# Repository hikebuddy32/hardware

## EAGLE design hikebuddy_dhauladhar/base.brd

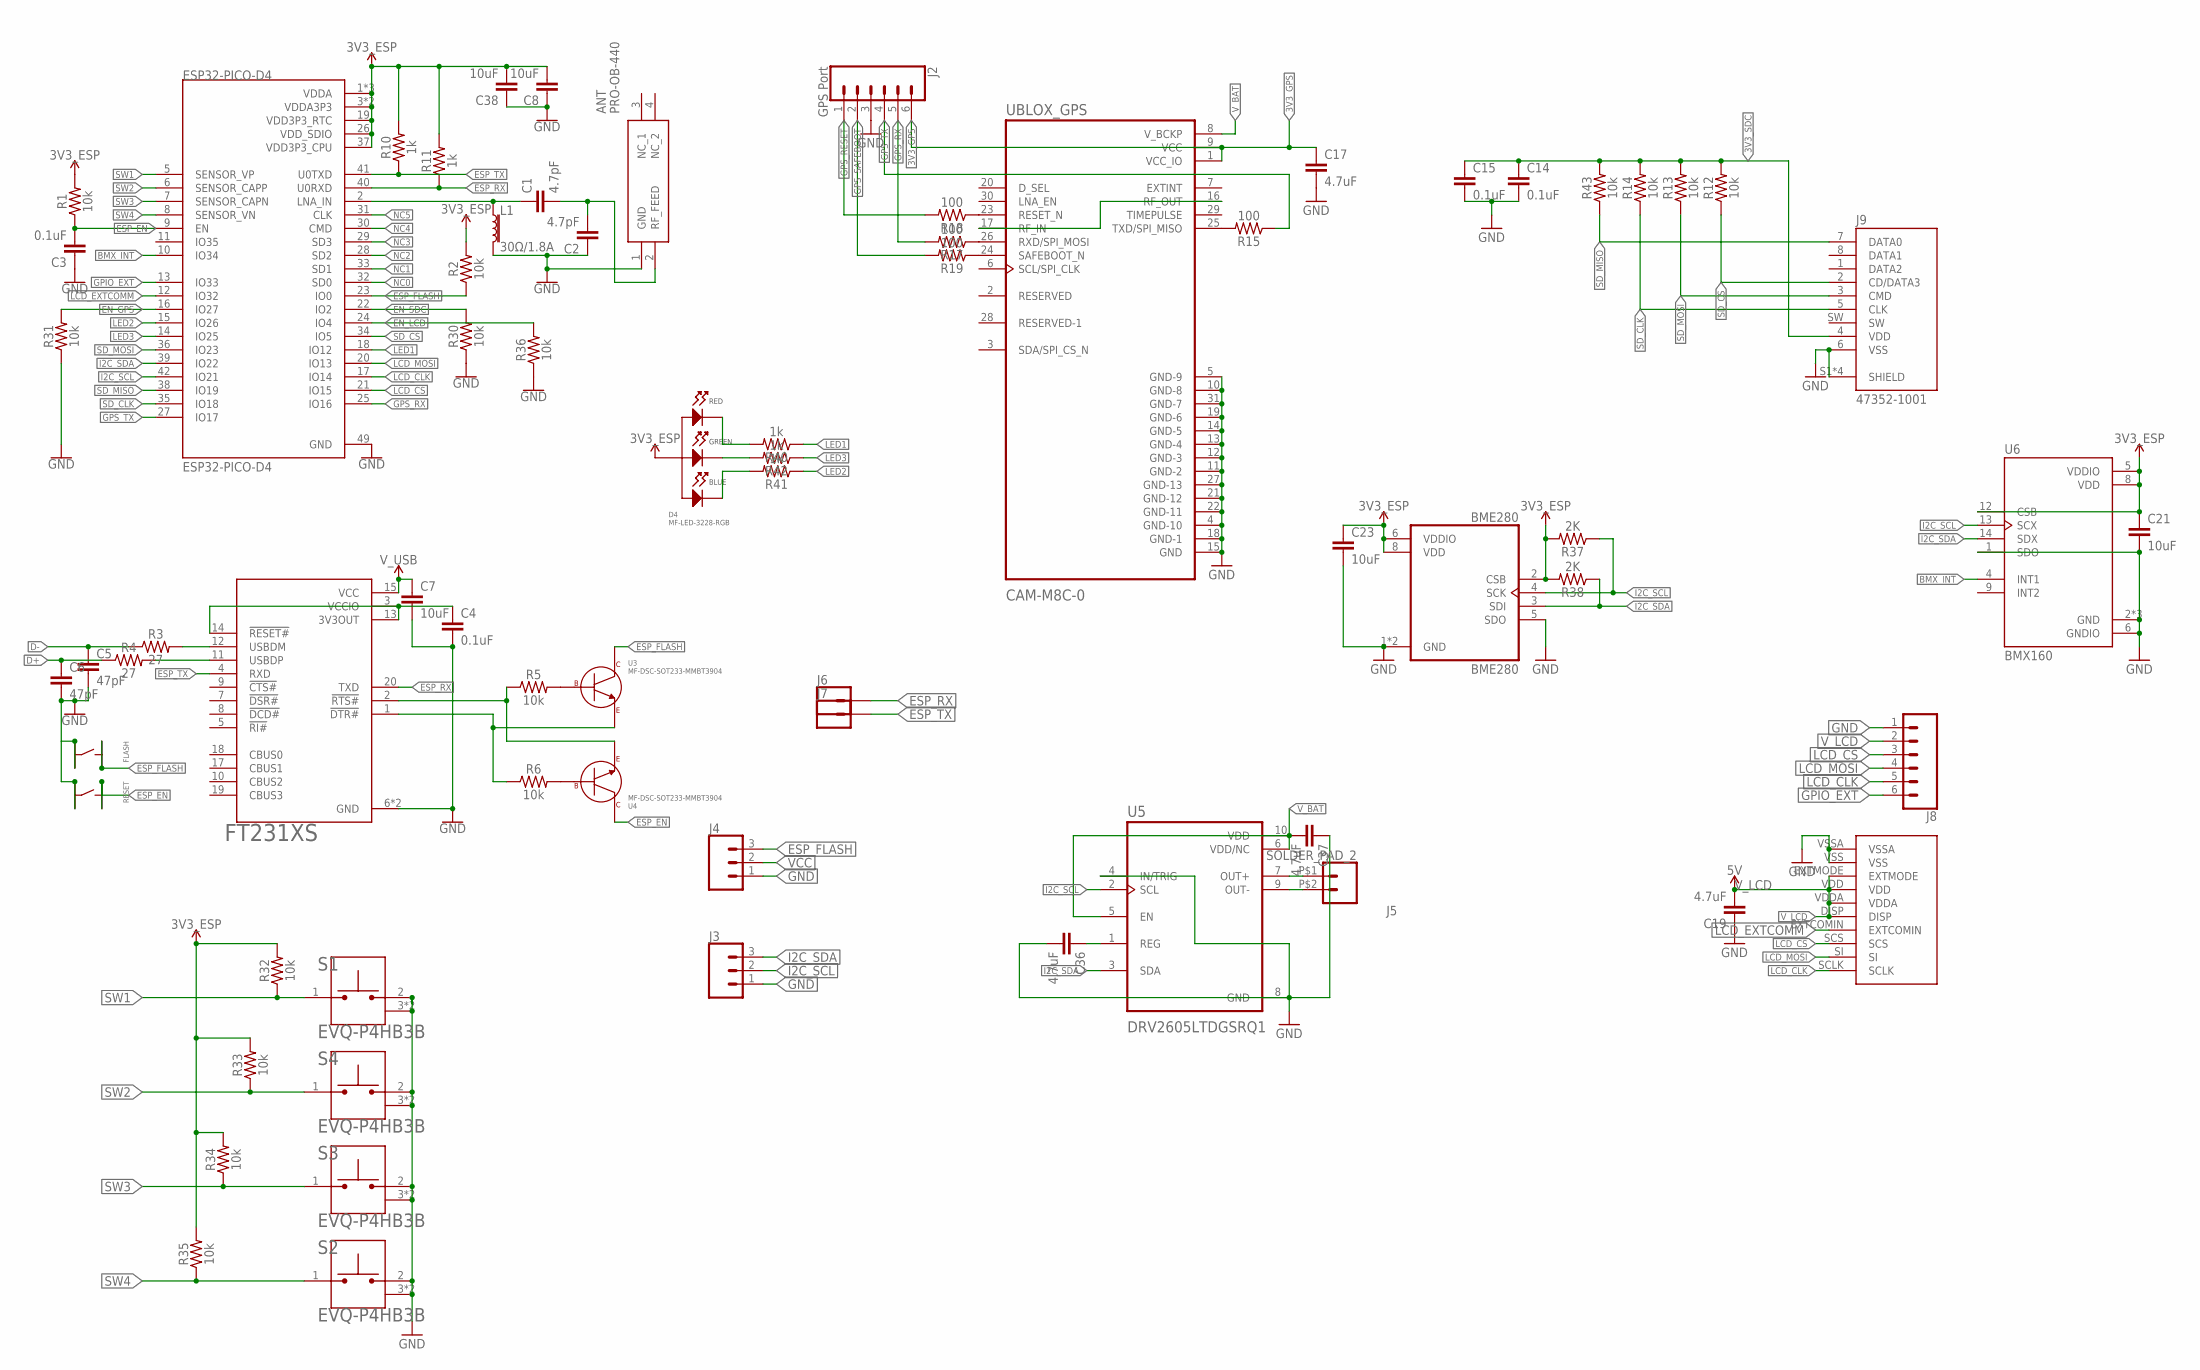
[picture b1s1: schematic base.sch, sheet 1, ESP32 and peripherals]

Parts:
ANT: PRO-OB-440; PRO-OB-440_1
BME280: BME280; PSON65P250X250X100-8N
C1, C2: 4.7pF; C0603
C3, C4, C14, C15: 0.1uF; C0603
C5, C6: 47pF; C0603
C7, C8, C21, C23, C38: 10uF; C0603
C17, C19, C36, C37: 4.7uF; C0603
D4: MF-LED-3228-RGB; PLCC4
ESP32-PICO-D4: ESP32-PICO-D4; PQFN50P700X700X104-49N
FLASH: MF-SW-TACT-4.2MM; TACT4.2MM
FT231: FT231XS; TSSOP20
J2: GPS Port; 1X06_LOCK
J3, J4: CONN_03LOCK; 1X03_LOCK
J5: SOLDER_PAD_2
J6, J7: CONN_01; 1X01
J8: CONN_06NO_SILK_NO_POP; 1X06_NO_SILK
J9: 47352-1001; MOLEX_47352-1001
L1: 30Ω/1.8A; L0603; MPN 744761016C
R1, R2, R5, R6, R12, R13, R14, R30, R31, R32, R33, R34, R35, R36, R43: 10k; R0603
R3, R4: 27; R0603
R10, R11, R40, R41, R42: 1k; R0603
R15, R17, R18, R19: 100; R0603
R37, R38: 2K; R0603
RESET: MF-SW-TACT-4.2MM; TACT4.2MM
S1, S2, S3, S4: EVQ-P4HB3B; SW_EVQ-P4HB3B
U3, U4: MF-DSC-SOT233-MMBT3904; SOT-23-3
U5: DRV2605LTDGSRQ1; SOP50P490X110-10N
U6: BMX160; PQFN50P250X300X100-14N
U$5: 51441-1093; FH12-10S-0.5SH; MPN 51441-1093
UBLOX_GPS: CAM-M8C-0; LCC100P960X1400X210-31N

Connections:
3V3_GPS: C17.1, J2.6, UBLOX_GPS.1 (VCC_IO), UBLOX_GPS.9 (VCC); also elsewhere on the board
3V3_SDC: C14.1, C15.1, J9.4 (VDD), R12.2, R13.2, R14.2, R43.2; also elsewhere on the board
BMX_INT: ESP32-PICO-D4.10 (IO34), U6.4 (INT1)
D+: C6.1, R4.1; also elsewhere on the board
D-: C5.1, R3.1; also elsewhere on the board
EN_GPS: ESP32-PICO-D4.16 (IO27), R31.2; also elsewhere on the board
EN_LCD: ESP32-PICO-D4.24 (IO4), R36.2; also elsewhere on the board
EN_SDC: ESP32-PICO-D4.22 (IO2), R30.2; also elsewhere on the board
ESP_EN: C3.2, ESP32-PICO-D4.9 (EN), R1.1, RESET.P$1, RESET.P$2, U4.P$3 (COLLECTOR)
ESP_FLASH: ESP32-PICO-D4.23 (IO0), FLASH.P$1, FLASH.P$2, J4.3, R2.1, U3.P$3 (COLLECTOR)
ESP_RX: ESP32-PICO-D4.40 (U0RXD), FT231.20 (TXD), J6.1, R11.1
ESP_TX: ESP32-PICO-D4.41 (U0TXD), FT231.4 (RXD), J7.1, R10.1
GND: ANT.1 (GND), BME280.1 (GND), BME280.5 (SDO), BME280.7 (GND), C2.1, C3.1, C4.2, C5.2, C6.2, C7.2, C8.1, C14.2, C15.2, C17.2, C19.1, C21.2, C23.2, C36.2, C37.1, C38.1, ESP32-PICO-D4.49 (GND), FLASH.P$3, FLASH.P$4, FT231.6 (GND), FT231.16 (GND), J2.3, J3.1, J4.1, J8.1, J9.6 (VSS), J9.S1 (SHIELD), J9.S2 (SHIELD), J9.S3 (SHIELD), J9.S4 (SHIELD), L1.2, R30.1, R31.1, R36.1, RESET.P$3, RESET.P$4, S1.2, S1.3 (SHIELD), S1.4 (SHIELD), S2.2, S2.3 (SHIELD), S2.4 (SHIELD), S3.2, S3.3 (SHIELD), S3.4 (SHIELD), S4.2, S4.3 (SHIELD), S4.4 (SHIELD), U5.4 (IN/TRIG), U5.8 (GND), U6.1 (SDO), U6.2 (GND), U6.3 (GND), U6.6 (GNDIO), U6.7 (GND), U$5.VSS, U$5.VSSA, UBLOX_GPS.4 (GND-10), UBLOX_GPS.5 (GND-9), UBLOX_GPS.10 (GND-8), UBLOX_GPS.11 (GND-2), UBLOX_GPS.12 (GND-3), UBLOX_GPS.13 (GND-4), UBLOX_GPS.14 (GND-5), UBLOX_GPS.15 (GND), UBLOX_GPS.18 (GND-1), UBLOX_GPS.19 (GND-6), UBLOX_GPS.21 (GND-12), UBLOX_GPS.22 (GND-11), UBLOX_GPS.27 (GND-13), UBLOX_GPS.31 (GND-7); also elsewhere on the board
GPIO_EXT: ESP32-PICO-D4.13 (IO33), J8.6
GPS_RESET: J2.1, R18.2
GPS_RX: ESP32-PICO-D4.25 (IO16), J2.5, R17.2
GPS_SAFEBOOT: J2.2, R19.2
GPS_TX: ESP32-PICO-D4.27 (IO17), J2.4, R15.1
I2C_SCL: BME280.4 (SCK), ESP32-PICO-D4.42 (IO21), J3.2, R37.1, U5.2 (SCL), U6.13 (SCX); also elsewhere on the board
I2C_SDA: BME280.3 (SDI), ESP32-PICO-D4.39 (IO22), J3.3, R38.1, U5.3 (SDA), U6.14 (SDX); also elsewhere on the board
LCD_CLK: ESP32-PICO-D4.17 (IO14), J8.5, U$5.SCLK
LCD_CS: ESP32-PICO-D4.21 (IO15), J8.3, U$5.SCS
LCD_EXTCOMM: ESP32-PICO-D4.12 (IO32), U$5.EXTCOMIN
LCD_MOSI: ESP32-PICO-D4.20 (IO13), J8.4, U$5.SI
LED1: ESP32-PICO-D4.18 (IO12), R40.1
LED2: ESP32-PICO-D4.15 (IO26), R41.1
LED3: ESP32-PICO-D4.14 (IO25), R42.1
unnamed: C1.1, ESP32-PICO-D4.2 (LNA_IN), L1.1
unnamed: ANT.2 (RF_FEED), C1.2, C2.2
unnamed: R5.2, U3.P$1 (BASE)
unnamed: R6.2, U4.P$1 (BASE)
unnamed: C4.1, FT231.3 (VCCIO), FT231.13 (3V3OUT), FT231.14 (!RESET#)
unnamed: FT231.12 (USBDM), R3.2
unnamed: FT231.11 (USBDP), R4.2
unnamed: FT231.2 (!RTS#), R5.1, U4.P$2 (EMITTER)
unnamed: FT231.1 (!DTR#), R6.1, U3.P$2 (EMITTER)
unnamed: D4.P$2 (CATHODE_RED), R40.2
unnamed: R15.2, UBLOX_GPS.25 (TXD/SPI_MISO)
unnamed: R17.1, UBLOX_GPS.26 (RXD/SPI_MOSI)
unnamed: D4.P$3 (CATHODE_GREEN), R42.2
unnamed: D4.P$4 (CATHODE_BLUE), R41.2
unnamed: UBLOX_GPS.16 (RF_OUT), UBLOX_GPS.17 (RF_IN)
unnamed: R18.1, UBLOX_GPS.23 (RESET_N)
unnamed: R19.1, UBLOX_GPS.24 (SAFEBOOT_N)
unnamed: C36.1, U5.1 (REG)
unnamed: J5.P$2 (2), U5.9 (OUT-)
unnamed: J5.P$1 (1), U5.7 (OUT+)
NC0: ESP32-PICO-D4.32 (SD0)
NC1: ESP32-PICO-D4.33 (SD1)
NC2: ESP32-PICO-D4.28 (SD2)
NC3: ESP32-PICO-D4.29 (SD3)
NC4: ESP32-PICO-D4.30 (CMD)
NC5: ESP32-PICO-D4.31 (CLK)
SD_CLK: ESP32-PICO-D4.35 (IO18), J9.5 (CLK), R14.1
SD_CS: ESP32-PICO-D4.34 (IO5), J9.2 (CD/DATA3), R12.1
SD_MISO: ESP32-PICO-D4.38 (IO19), J9.7 (DATA0), R43.1
SD_MOSI: ESP32-PICO-D4.36 (IO23), J9.3 (CMD), R13.1
SW1: ESP32-PICO-D4.5 (SENSOR_VP), R32.1, S1.1
SW2: ESP32-PICO-D4.6 (SENSOR_CAPP), R33.1, S4.1
SW3: ESP32-PICO-D4.7 (SENSOR_CAPN), R34.1, S3.1
SW4: ESP32-PICO-D4.8 (SENSOR_VN), R35.1, S2.1
VCC: BME280.2 (CSB), BME280.6 (VDDIO), BME280.8 (VDD), C8.2, C21.1, C23.1, C38.2, D4.P$1 (ANODE), ESP32-PICO-D4.1 (VDDA), ESP32-PICO-D4.3 (VDDA3P3), ESP32-PICO-D4.4 (VDDA3P3), ESP32-PICO-D4.19 (VDD3P3_RTC), ESP32-PICO-D4.26 (VDD_SDIO), ESP32-PICO-D4.37 (VDD3P3_CPU), ESP32-PICO-D4.43 (VDDA), ESP32-PICO-D4.46 (VDDA), J4.2, R1.2, R2.2, R10.2, R11.2, R32.2, R33.2, R34.2, R35.2, R37.2, R38.2, U6.5 (VDDIO), U6.8 (VDD), U6.12 (CSB); also elsewhere on the board
V_BAT: C37.2, U5.5 (EN), U5.6 (VDD/NC), U5.10 (VDD), UBLOX_GPS.8 (V_BCKP); also elsewhere on the board
V_LCD: C19.2, J8.2, U$5.DISP, U$5.EXTMODE, U$5.VDD, U$5.VDDA; also elsewhere on the board
V_USB: C7.1, FT231.15 (VCC); also elsewhere on the board

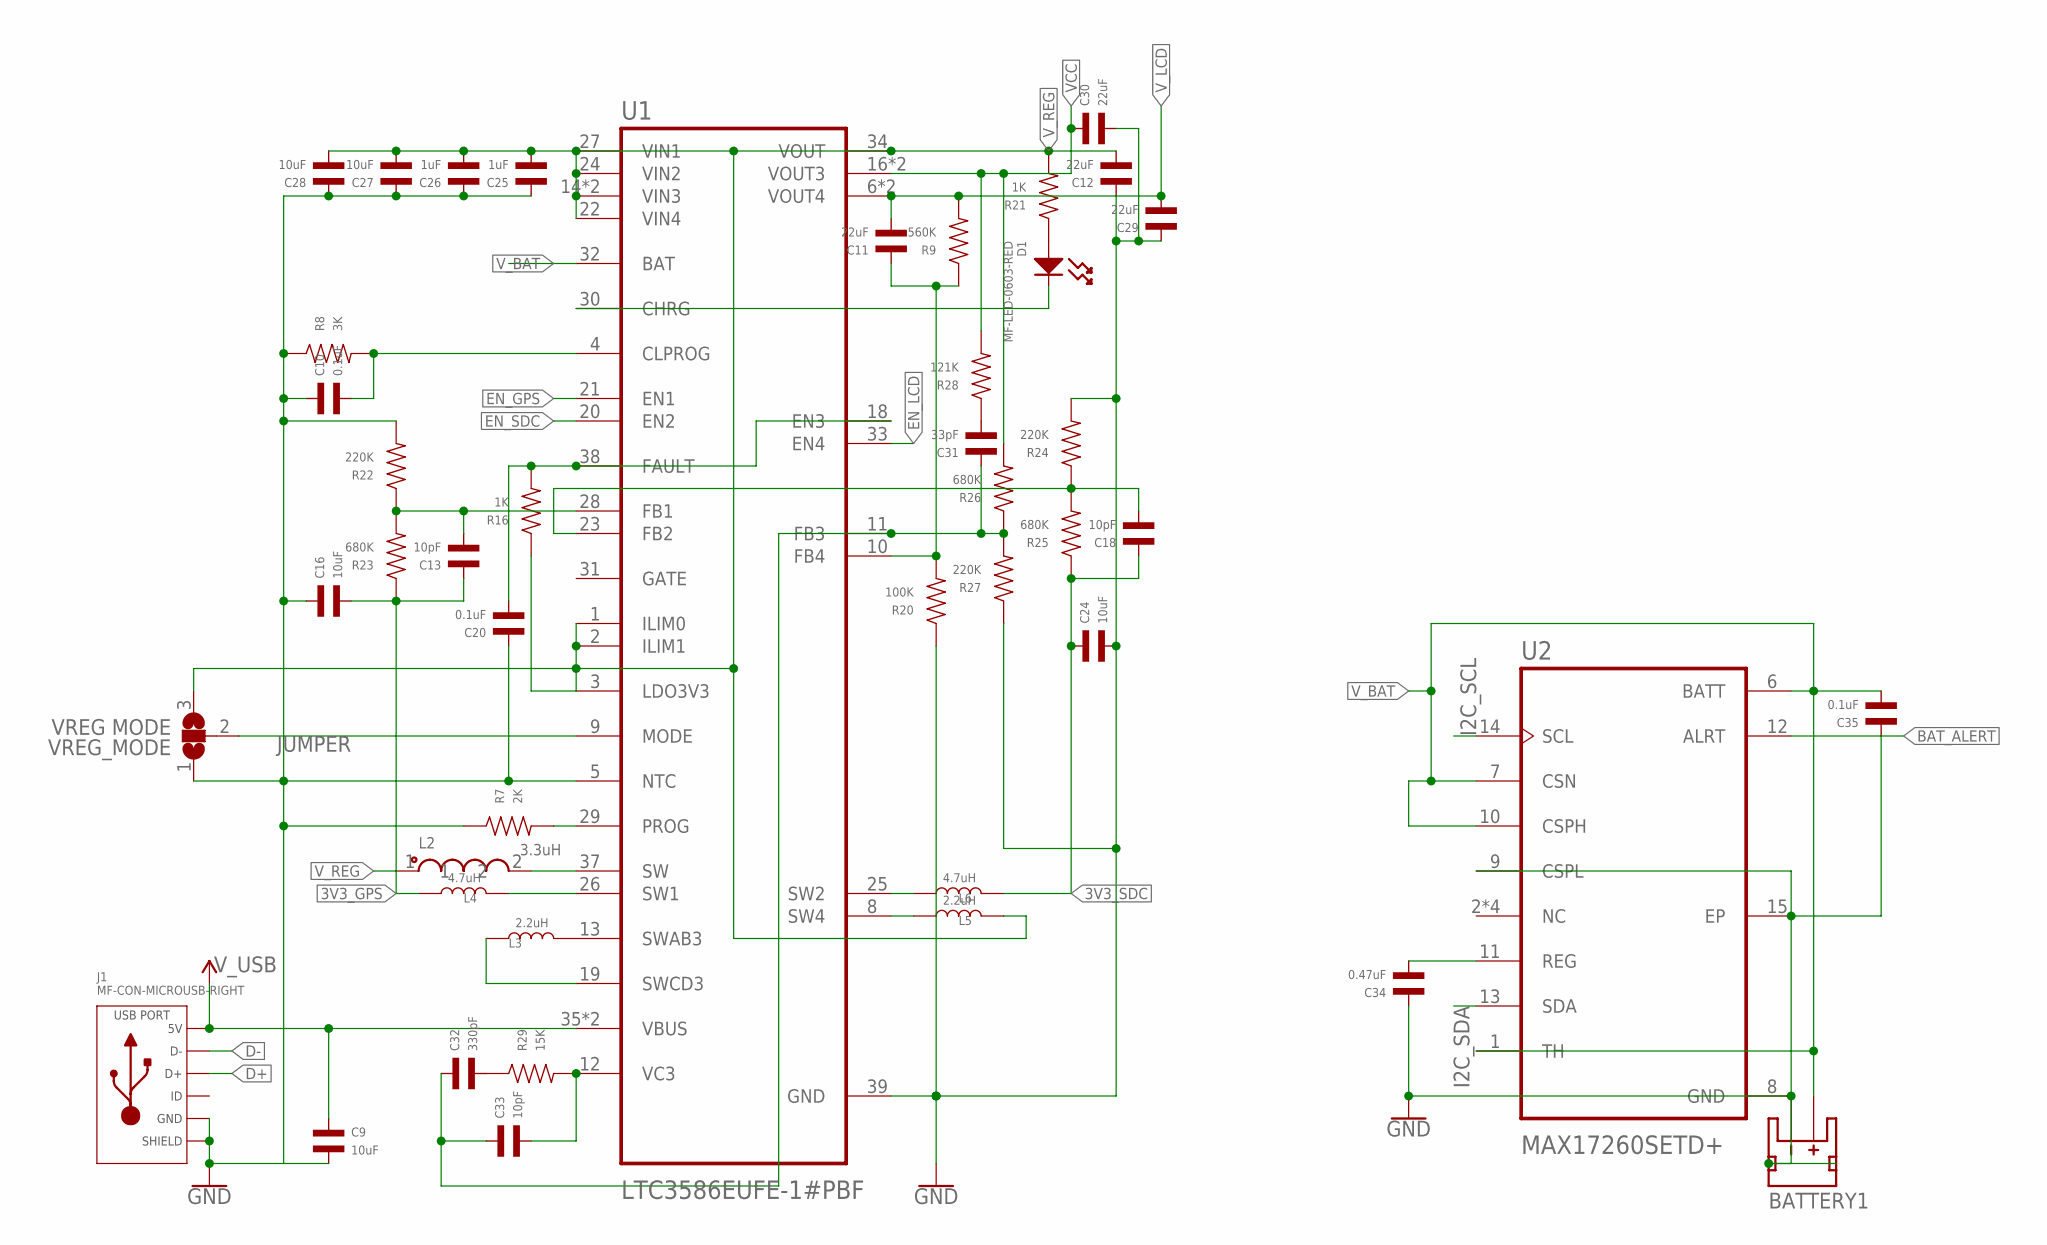
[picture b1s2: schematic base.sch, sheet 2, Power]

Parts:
BATTERY1: S2B-PH-SM4-TB(LF)(SN); JST-2-SMD
C9, C16, C24, C27, C28: 10uF; C0603
C10, C20, C35: 0.1uF; C0603
C11, C12, C29, C30: 22uF; C0603
C13, C18, C33: 10pF; C0603
C25, C26: 1uF; C0603
C31: 33pF; C0603
C32: 330pF; C0603
C34: 0.47uF; C0603
D1: MF-LED-0603-RED; LED0603
J1: MF-CON-MICROUSB-RIGHT; MICROUSB-RIGHT
L2: 3.3uH; INDP_LPS4018-472MRB; MPN LPS4018-472MRB
L3, L5: 2.2uH; L1210; MPN L1210R2R2MDWIT
L4, L6: 4.7uH; L1210; MPN L1210R4R7MDWIT
R7: 2K; R0603
R8: 3K; R0603
R9: 560K; R0603
R16, R21: 1K; R0603
R20: 100K; R0603
R22, R24, R27: 220K; R0603
R23, R25, R26: 680K; R0603
R28: 121K; R0603
R29: 15K; R0603
U1: LTC3586EUFE-1#PBF; QFN40P600X400X80-39N
U2: MAX17260SETD+; SON40P300X300X80-15N
VREG_MODE: VREG MODE; SJ_2

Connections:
3V3_GPS: C13.P$1, C16.P$2, L4.P$1, R23.P$1; also elsewhere on the board
3V3_SDC: C18.P$1, C24.P$1, L6.P$2, R25.P$1; also elsewhere on the board
BAT_ALERT: U2.12 (ALRT)
D+: J1.3 (D+); also elsewhere on the board
D-: J1.2 (D-); also elsewhere on the board
EN_GPS: U1.21 (EN1); also elsewhere on the board
EN_LCD: U1.33 (EN4); also elsewhere on the board
EN_SDC: U1.20 (EN2); also elsewhere on the board
GND: BATTERY1.1 (-), BATTERY1.NC1 (PAD1), BATTERY1.NC2 (PAD2), C9.P$2, C10.P$1, C12.P$1, C16.P$1, C20.P$1, C24.P$2, C25.P$1, C26.P$1, C27.P$1, C28.P$1, C29.P$1, C30.P$2, C34.P$1, C35.P$1, J1.5 (GND), J1.S1 (SLD), J1.S2 (SLD), J1.S3 (SLD), J1.S4 (SLD), J1.S5 (SLD), J1.S6 (SLD), R7.P$1, R8.P$1, R20.P$1, R22.P$2, R24.P$2, R27.P$1, U1.5 (NTC), U1.39 (GND), U2.8 (GND), U2.9 (CSPL), U2.15 (EP), VREG_MODE.1; also elsewhere on the board
I2C_SCL: U2.14 (SCL); also elsewhere on the board
I2C_SDA: U2.13 (SDA); also elsewhere on the board
JUMPER: U1.9 (MODE), VREG_MODE.2
unnamed: R7.P$2, U1.29 (PROG)
unnamed: C10.P$2, R8.P$2, U1.4 (CLPROG)
unnamed: C11.P$1, R9.P$1, R20.P$2, U1.10 (FB4)
unnamed: L3.P$2, U1.13 (SWAB3)
unnamed: C31.P$1, C32.P$1, C33.P$1, R26.P$1, R27.P$2, U1.11 (FB3)
unnamed: L2.2, U1.37 (SW)
unnamed: D1.CATHODE, U1.30 (CHRG)
unnamed: D1.ANODE, R21.P$1
unnamed: L3.P$1, U1.19 (SWCD3)
unnamed: C20.P$2, R16.P$2, U1.18 (EN3), U1.38 (FAULT)
unnamed: L4.P$2, U1.26 (SW1)
unnamed: C13.P$2, R22.P$1, R23.P$2, U1.28 (FB1)
unnamed: L5.P$1, U1.8 (SW4)
unnamed: C18.P$2, R24.P$1, R25.P$2, U1.23 (FB2)
unnamed: L6.P$1, U1.25 (SW2)
unnamed: C31.P$2, R28.P$1
unnamed: C33.P$2, R29.P$2, U1.12 (VC3)
unnamed: C32.P$2, R29.P$1
unnamed: C34.P$2, U2.11 (REG)
VCC: C30.P$1, R26.P$2, R28.P$2, U1.16 (VOUT3), U1.17 (VOUT3); also elsewhere on the board
V_BAT: BATTERY1.2 (+), C35.P$2, U1.32 (BAT), U2.1 (TH), U2.6 (BATT), U2.7 (CSN), U2.10 (CSPH); also elsewhere on the board
V_LCD: C11.P$2, C29.P$2, R9.P$2, U1.6 (VOUT4), U1.7 (VOUT4); also elsewhere on the board
V_REG: C12.P$2, C25.P$2, C26.P$2, C27.P$2, C28.P$2, L2.1, L5.P$2, R16.P$1, R21.P$2, U1.1 (ILIM0), U1.2 (ILIM1), U1.3 (LDO3V3), U1.14 (VIN3), U1.15 (VIN3), U1.22 (VIN4), U1.24 (VIN2), U1.27 (VIN1), U1.34 (VOUT), VREG_MODE.3
V_USB: C9.P$1, J1.1 (5V), U1.35 (VBUS), U1.36 (VBUS); also elsewhere on the board

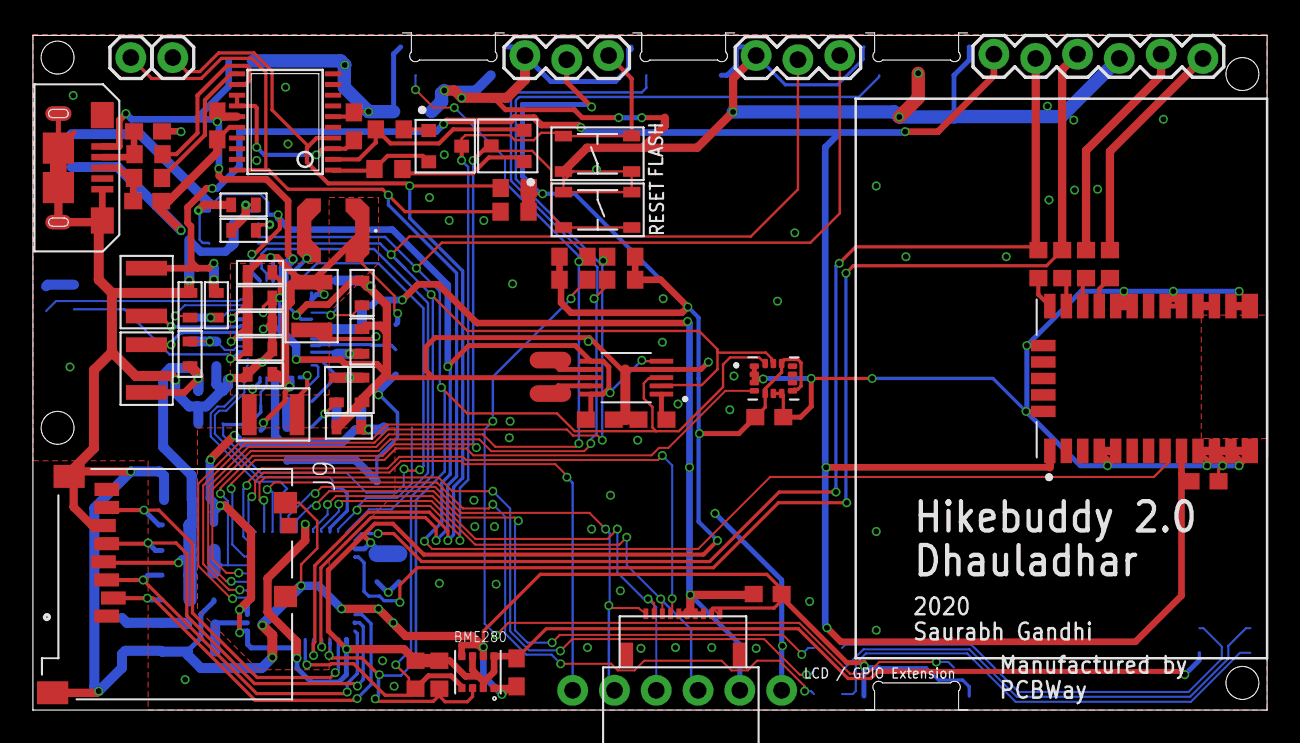
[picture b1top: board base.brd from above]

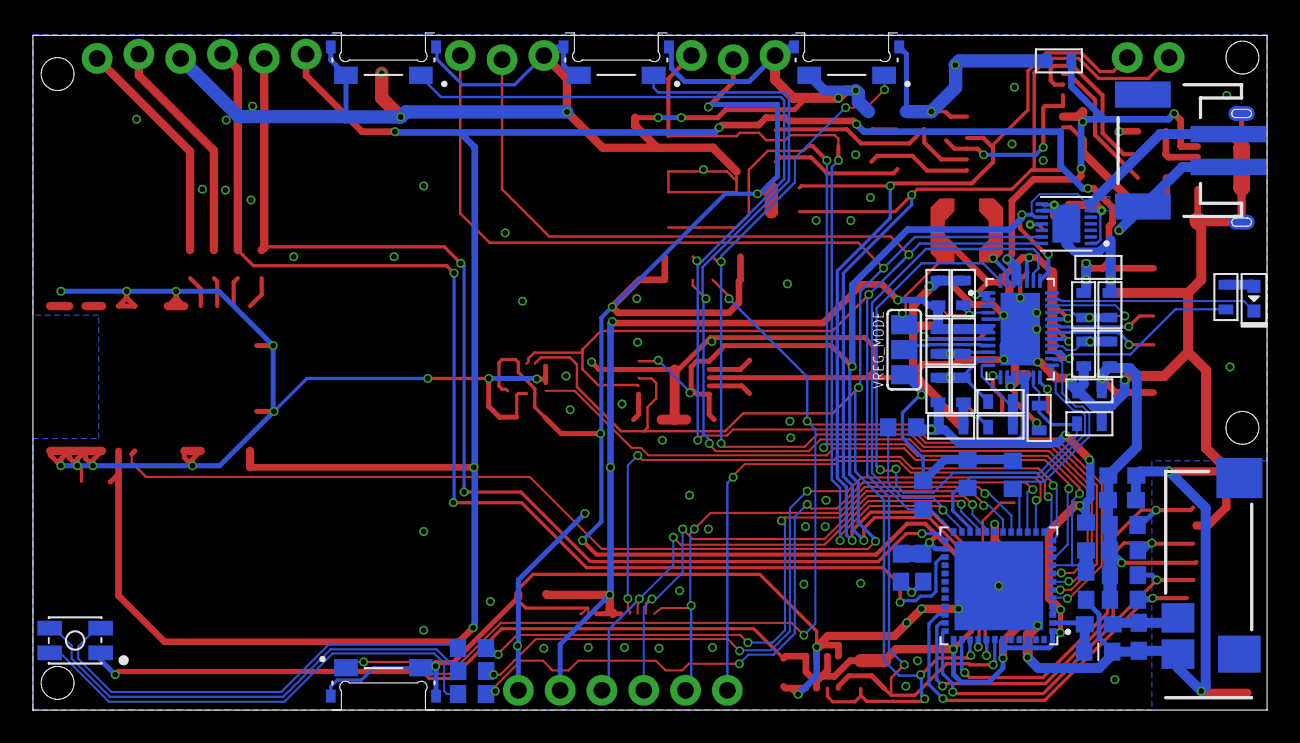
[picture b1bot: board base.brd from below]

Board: 2 copper layers, 75.0 x 41.0 mm, 116 parts (51 on the bottom side), 80 nets.

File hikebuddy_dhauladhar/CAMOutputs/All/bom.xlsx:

Qty | Value | Device | Package | Designator | Description | MANUFACTURER_NAME | MANUFACTURER_PART_NUMBER
1 | LTC3586EUFE | LTC3586EUFE | QFN -38 Analog Devices | U1 | USB Power Manager 4.35V to 5.5V 38-Pin QFN EP T/R | Analog Devices | LTC3586EUFE
6 | 0.1uF | CAPACITOR_NP_0603 | C0603 | C3, C4, C10, C14, C15, C35 | Library: MF_Passives |  | CC0603ZRY5V8BB104
1 | 0.47uF | CAPACITOR_NP_0603 | C0603 | C34 | Library: MF_Passives |  | CC0603ZRY5V6BB474
4 | 100 | RESISTOR_0603 | R0603 | R15, R17, R18, R19 | Library: MF_Passives |  | RC0603FR-07100RL
1 | 100K | RESISTOR_0603 | R0603 | R20 | Library: MF_Passives |  | RT0603BRD07100KL
12 | 10k | RESISTOR_0603 | R0603 | R1, R2, R5, R6, R12, R13, R14, R16, R30, R31, R36, R43 | Library: MF_Passives |  | RC0603FR-0710KL
3 | 10pF | CAPACITOR_NP_0603 | C0603 | C13, C18, C33 | Library: MF_Passives |  | CC0603JRNPO9BN100
10 | 10uF | CAPACITOR_NP_0603 | C0603 | C7, C8, C9, C16, C21, C23, C24, C27, C28, C38 | Library: MF_Passives |  | CC0603KRX5R5BB106
1 | 121K | RESISTOR_0603 | R0603 | R28 | Library: MF_Passives |  | RC0603FR-07121KL
1 | 15K | RESISTOR_0603 | R0603 | R29 | Library: MF_Passives |  | RC0603FR-0715KL
6 | 1k | RESISTOR_0603 | R0603 | R10, R11, R21, R40, R41, R42 | Library: MF_Passives |  | RC0603FR-071KL
3 | 1uF | CAPACITOR_NP_0603 | C0603 | C20, C25, C26 | Library: MF_Passives |  | CC0603KRX5R8BB105
2 | 2.2uH | INDUCTOR_1210 | L1210 | L3, L5 | Library: MF_Passives |  | L1210R2R2MDWIT
3 | 220K | RESISTOR_0603 | R0603 | R22, R24, R27 | Library: MF_Passives |  | AC0603FR-07220KL
4 | 22uF | CAPACITOR_NP_0603 | C0603 | C11, C12, C29, C30 | Library: MF_Passives |  | CC0603MRX5R5BB226
2 | 27 | RESISTOR_0603 | R0603 | R3, R4 | Library: MF_Passives |  | RC0603FR-0727RL
3 | 2K | RESISTOR_0603 | R0603 | R7, R37, R38 | Library: MF_Passives |  | RC0603FR-072KL
1 | 3.3uH | LPS4018-332MRB | INDP_LPS4018-472MRB | L2 | Power inductor, shielded, 20/30% tol, SMT, RoHS, lead-free, halogen-free | Coilcraft | LPS4018-332MRB
1 | 1.6nH | INDUCTOR_0603 | L0603 | L1 | Library: MF_Passives |  | 744761016C
1 | 330pF | CAPACITOR_NP_0603 | C0603 | C32 | Library: MF_Passives |  | CC0603KRX7R9BB331
1 | 33pF | CAPACITOR_NP_0603 | C0603 | C31 | Library: MF_Passives |  | CC0603JRNPO9BN330
1 | 3K | RESISTOR_0603 | R0603 | R8 | Library: MF_Passives |  | RT0603BRD073KL
2 | 4.7pF | CAPACITOR_NP_0603 | C0603 | C1, C2 | 4.7pF ceramic capacitors |  | CC0603CRNPO9BN4R7
4 | 4.7uF | CAPACITOR_NP_0603 | C0603 | C17, C19, C36, C37 | 4.7ÂµF ceramic capacitors |  | CC0603KRX5R6BB475
2 | 4.7uH | INDUCTOR_1210 | L1210 | L4, L6 | Library: MF_Passives |  | L1210R4R7MDWIT
2 | 47pF | CAPACITOR_NP_0603 | C0603 | C5, C6 | 47pF ceramic capacitors |  | CC0603JRNPO9BN470
1 | 51441-1093 | LS027B_LCD_SHARPFH12-10S-0.5SH | FH12-10S-0.5SH | U$5 |  | Molex | 51441-1093
1 | 560K | RESISTOR_0603 | R0603 | R9 | Library: MF_Passives |  | RC0603FR-07560KL
3 | 680K | RESISTOR_0603 | R0603 | R23, R25, R26 | Library: MF_Passives |  | RC0603FR-07680KL
1 | BME280 | BME280 | LGA-8 | BME280 | DIGITAL HUMIDITY, PRESSURE AND TEMPERATURE SENSOR* Digital interface IÂ²C (up t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 | Bosch | BME280
1 | BMX160 | BMX160 | VFLGA-14 Bosch Sensortec | U6 | IMU ACCEL/GYRO/MAG | Bosch Sensortec | BMX160
1 | CAM-M8C-0 | CAM-M8C-0 | SMD-31 u-blox | UBLOX_GPS | Ic Receiver Gps Chip Ant 31lcc | U-Blox America | CAM-M8C-0
1 | DRV2605LTDGSRQ1 | DRV2605LTDGSRQ1 | TFSOP-10 Texas Instruments | U5 | Haptic Driver for ERM and LRA With Built-In Library and Smart Loop A 10-VSSOP -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 | Texas Instruments | DRV2605LTDGSRQ1
1 | ESP32-PICO-D4 | ESP32-PICO-D4 | SMD-48 Espressif Systems | ESP32-PICO-D4 | The ESP32-PICO-D4 is a System-in-Package (SIP) module that is based on ESP32, p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 | Espressif Systems | ESP32-PICO-D4
4 | EVQ-P4HB3B | EVQ-P4HB3B | SW_EVQ-P4HB3B | S1, S2, S3, S4 | Light Touch Switch, 3.5x2.9mm Right Angl Side-operational L-Shape, Force=2.2N, 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 | Panasonic Electronic | EVQ-P4HB3B
1 | FT231XS | FT231XS-UTSSOP20 | TSSOP20 | FT231 | USB Full Speed to Full Handshake UART with USB Charger Detection, SSOP-20 |  | FT231XS-U
1 | MAX17260SETD+ | MAX17260SETD+ | TDFN-14 Maxim | U2 | Fuel Gauge Li+/LiFePO4 1-Cell 2-Wire Interface 5.1uA 0.4V 14-Pin TDFN-EP Tube | Maxim Integrated | MAX17260SETD+
1 | MF-CON-MICROUSB-RIGHT | USB_MICRO_RIGHT | MICROUSB-RIGHT | J1 | Library: MF_Connectors |  | MF-CON-MICROUSB-RIGHT
2 | MF-DSC-SOT233-MMBT3904 | NPN_BJTMMBT3904_SOT-23-3 | SOT-23-3 | U3, U4 | Library: MF_Discrete_Semiconductor |  | MF-DSC-SOT233-MMBT3904
1 | MF-LED-0603-RED | LED_SINGLE-0603-RED | LED0603 | D1 | Library: MF_LEDs |  | MF-LED-0603-RED
1 | MF-LED-3228-RGB | LED_RGB_CA_PLCC4 | PLCC4 | D4 | Library: MF_LEDs |  | MF-LED-3228-RGB
1 | MF-MICROSD | SD_CARD_SLOT_MICRO_RIGHT | MF-MICROSD | SD1 | Library: MF_Connectors |  | MF-MICROSD
2 | MF-SW-TACT-4.2MM | TACT_4.2MM | TACT4.2MM | FLASH, RESET | Library: MF_Switches |  | MF-SW-TACT-4.2MM
1 | PRO-OB-440 | PRO-OB-440 | PRO-OB-440_1 | ANT | OnBoard SMD 2400 antenna | Proant AB | PRO-OB-440
1 | S2B-PH-SM4-TB(LF)(SN) | JST_2MM_MALE | JST-2-SMD | BATTERY1 | JST 2MM MALE RA CONNECTOR |  | S2B-PH-SM4-TB(LF)(SN)

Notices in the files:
parts and their libraries:
SparkFun-Capacitors: Licensing: Creative Commons ShareAlike 4.0 International - https://creativecommons.org/licenses/by-sa/4.0
